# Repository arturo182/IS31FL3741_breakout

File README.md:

# IS31FL3741 PMOD Breakout Board

This is a simple breakout board for the IS31FL3741 39x9 Matrix LED Driver IC.

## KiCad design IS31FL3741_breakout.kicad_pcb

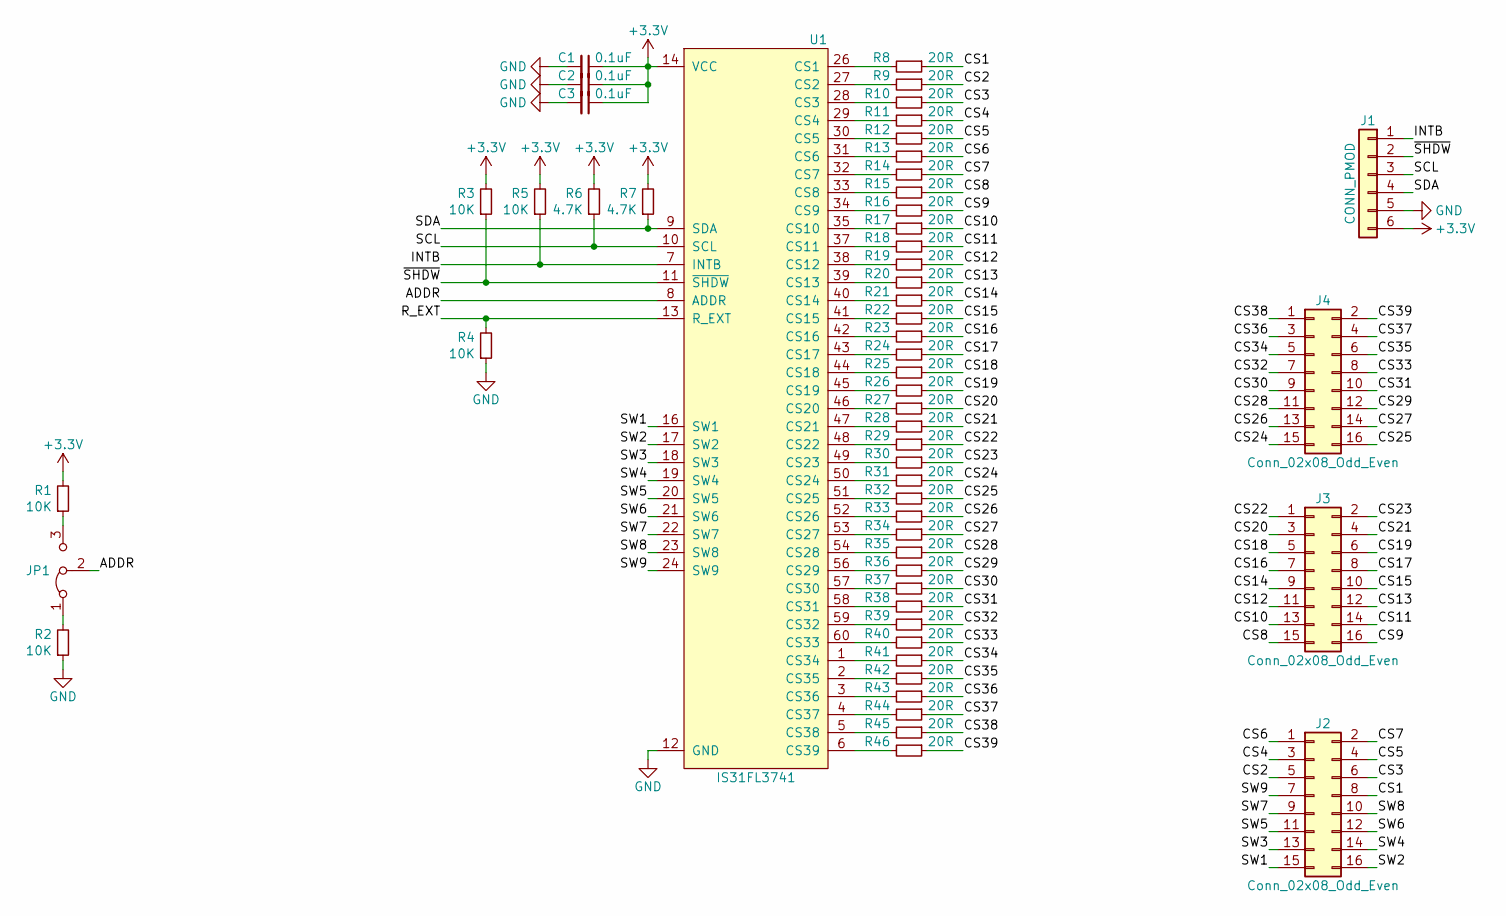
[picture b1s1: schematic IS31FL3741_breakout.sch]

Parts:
C1, C2, C3: 0.1uF; C_0603_1608Metric
J1: CONN_PMOD; PMODPinHeader_1x06_P2.54mm_Horizontal
J2, J3, J4: Conn_02x08_Odd_Even; PinHeader_2x08_P2.54mm_Vertical
JP1: JP_ADDR; SolderJumper-3_P1.3mm_Bridged12_RoundedPad1.0x1.5mm
R1, R2, R3, R4, R5: 10K; R_0603_1608Metric
R6, R7: 4.7K; R_0603_1608Metric
R8, R9, R10, R11, R12, R13, R14, R15, R16, R17, R18, R19, R20, R21, R22, R23, R24, R25, R26, R27, R28, R29, R30, R31, R32, R33, R34, R35, R36, R37, R38, R39, R40, R41, R42, R43, R44, R45, R46: 20R; R_0603_1608Metric
U1: IS31FL3741; QFN-60_EP_7x7_Pitch0.4mm

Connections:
+3V3: C1.1, C2.1, C3.1, J1.6, R1.2, R3.2, R5.2, R6.2, R7.2, U1.14 (VCC), U1.15 (VCC), U1.25 (VCC)
/ADDR: JP1.2 (C), U1.8 (ADDR)
/CS1: J2.8, R8.1
/CS2: J2.5, R9.1
/CS3: J2.6, R10.1
/CS4: J2.3, R11.1
/CS5: J2.4, R12.1
/CS6: J2.1, R13.1
/CS7: J2.2, R14.1
/CS8: J3.15, R15.1
/CS9: J3.16, R16.1
/CS10: J3.13, R17.1
/CS11: J3.14, R18.1
/CS12: J3.11, R19.1
/CS13: J3.12, R20.1
/CS14: J3.9, R21.1
/CS15: J3.10, R22.1
/CS16: J3.7, R23.1
/CS17: J3.8, R24.1
/CS18: J3.5, R25.1
/CS19: J3.6, R26.1
/CS20: J3.3, R27.1
/CS21: J3.4, R28.1
/CS22: J3.1, R29.1
/CS23: J3.2, R30.1
/CS24: J4.15, R31.1
/CS25: J4.16, R32.1
/CS26: J4.13, R33.1
/CS27: J4.14, R34.1
/CS28: J4.11, R35.1
/CS29: J4.12, R36.1
/CS30: J4.9, R37.1
/CS31: J4.10, R38.1
/CS32: J4.7, R39.1
/CS33: J4.8, R40.1
/CS34: J4.5, R41.1
/CS35: J4.6, R42.1
/CS36: J4.3, R43.1
/CS37: J4.4, R44.1
/CS38: J4.1, R45.1
/CS39: J4.2, R46.1
/INTB: J1.1, R5.1, U1.7 (INTB)
/R_EXT: R4.2, U1.13 (R_EXT)
/SCL: J1.3, R6.1, U1.10 (SCL)
/SDA: J1.4, R7.1, U1.9 (SDA)
/SW1: J2.15, U1.16 (SW1)
/SW2: J2.16, U1.17 (SW2)
/SW3: J2.13, U1.18 (SW3)
/SW4: J2.14, U1.19 (SW4)
/SW5: J2.11, U1.20 (SW5)
/SW6: J2.12, U1.21 (SW6)
/SW7: J2.9, U1.22 (SW7)
/SW8: J2.10, U1.23 (SW8)
/SW9: J2.7, U1.24 (SW9)
/~SHDW~: J1.2, R3.1, U1.11 (~SHDW~)
GND: C1.2, C2.2, C3.2, J1.5, R2.1, R4.1, U1.12 (GND), U1.36 (GND), U1.55 (GND), U1.61 (GND)
unnamed: JP1.1 (A), R2.2
unnamed: JP1.3 (B), R1.1
unnamed: R8.2, U1.26 (CS1)
unnamed: R9.2, U1.27 (CS2)
unnamed: R10.2, U1.28 (CS3)
unnamed: R11.2, U1.29 (CS4)
unnamed: R12.2, U1.30 (CS5)
unnamed: R13.2, U1.31 (CS6)
unnamed: R14.2, U1.32 (CS7)
unnamed: R15.2, U1.33 (CS8)
unnamed: R16.2, U1.34 (CS9)
unnamed: R17.2, U1.35 (CS10)
unnamed: R18.2, U1.37 (CS11)
unnamed: R19.2, U1.38 (CS12)
unnamed: R20.2, U1.39 (CS13)
unnamed: R21.2, U1.40 (CS14)
unnamed: R22.2, U1.41 (CS15)
unnamed: R23.2, U1.42 (CS16)
unnamed: R24.2, U1.43 (CS17)
unnamed: R25.2, U1.44 (CS18)
unnamed: R26.2, U1.45 (CS19)
unnamed: R27.2, U1.46 (CS20)
unnamed: R28.2, U1.47 (CS21)
unnamed: R29.2, U1.48 (CS22)
unnamed: R30.2, U1.49 (CS23)
unnamed: R31.2, U1.50 (CS24)
unnamed: R32.2, U1.51 (CS25)
unnamed: R33.2, U1.52 (CS26)
unnamed: R34.2, U1.53 (CS27)
unnamed: R35.2, U1.54 (CS28)
unnamed: R36.2, U1.56 (CS29)
unnamed: R37.2, U1.57 (CS30)
unnamed: R38.2, U1.58 (CS31)
unnamed: R39.2, U1.59 (CS32)
unnamed: R40.2, U1.60 (CS33)
unnamed: R41.2, U1.1 (CS34)
unnamed: R42.2, U1.2 (CS35)
unnamed: R43.2, U1.3 (CS36)
unnamed: R44.2, U1.4 (CS37)
unnamed: R45.2, U1.5 (CS38)
unnamed: R46.2, U1.6 (CS39)

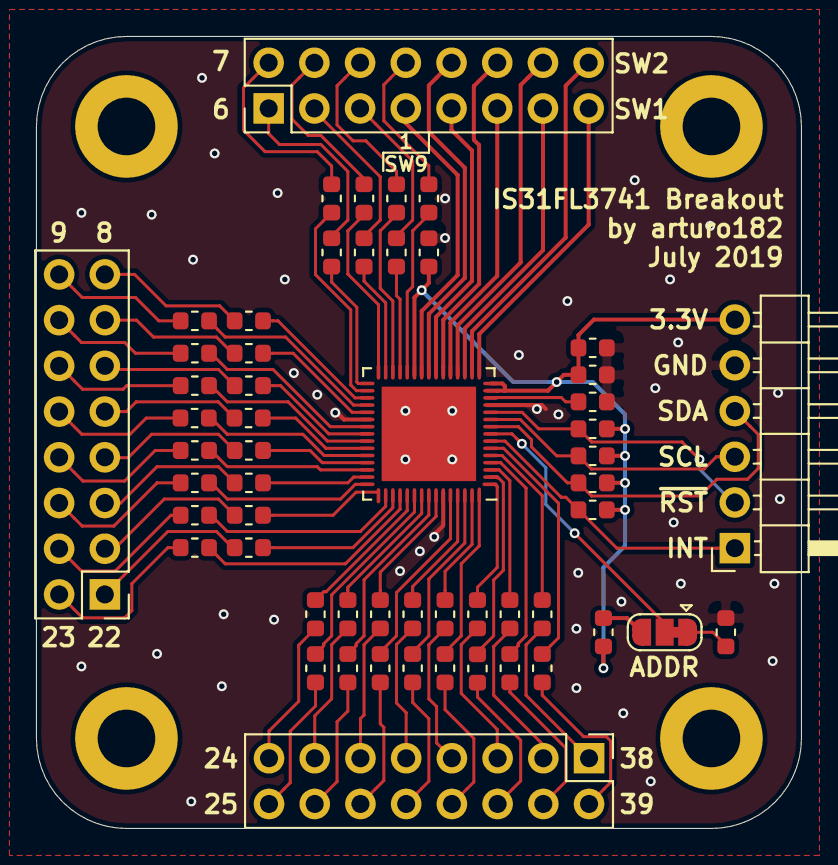
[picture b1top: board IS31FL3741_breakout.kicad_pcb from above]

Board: 2 copper layers, 42.5 x 44.0 mm, 55 parts (0 on the bottom side), 97 nets.

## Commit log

2019-05-29 Initial import
2019-05-29 Add schematic, bom, step file, readme and images
2019-07-03 Fix the QFN pin length
